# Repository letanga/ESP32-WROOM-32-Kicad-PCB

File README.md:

# ESP32-WROOM-32-Kicad-PCB
esp32开发板kicad PCB项目

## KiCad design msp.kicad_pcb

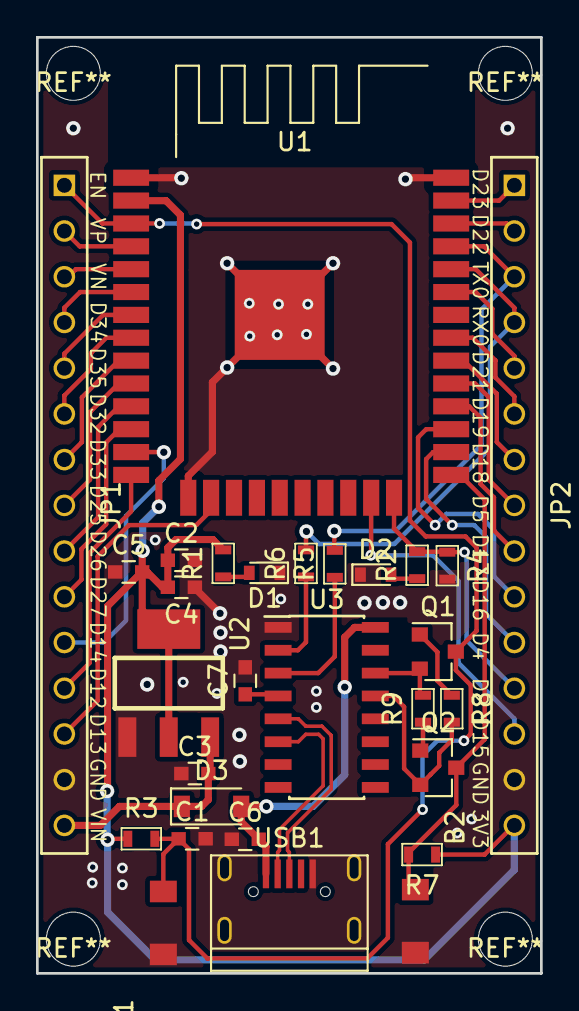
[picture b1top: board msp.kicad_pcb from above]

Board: 2 copper layers, 28.0 x 52.0 mm, 29 parts (0 on the bottom side), 42 nets.

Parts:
B1, B2: Button_2; buttton-2P
C1: 10uf; C_0603
C2, C5: 0.1uF; C_0603
C3, C4: 10uF; C_0603
C6, C7: 0.1UF; C_0603
D1, D2: LED; D_0603
D3: S4; D_SOD-123
JP1, JP2: JACK_PIN15; DIP-1.5Hole-2.54mm-Pitch-15P
Q1, Q2: S8050; SOT-23
R1, R2, R5, R6: 1K; R_0603
R3, R4, R7: 10K; R_0603
R8, R9: 10k; R_0603
U1: ESP32; ESP32-WROOM-32
U2: AMS1117-3.3; SOT-223
U3: CH340C; SOIC-16_3.9x9.9mm_Pitch1.27mm
USB1: Micro-B-USB; USB_Micro-B

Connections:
+3V3: C2.1, C4.2, C5.2, JP2.15, R1.2, R3.1, R7.1, U1.2, U2.2
/ESP32/D+: U3.5, USB1.3
/ESP32/D-: U3.6, USB1.2
/ESP32/DTR: Q2.2, R8.2, U3.13
/ESP32/EN: B1.2, C1.1, JP1.1, Q1.3, R3.2, U1.3
/ESP32/IO0: B2.1, Q2.3, R7.2, U1.25
/ESP32/IO1: JP2.3, R5.2, U1.35
/ESP32/IO2: JP2.12, R2.2, R4.1, U1.24
/ESP32/IO3: JP2.4, R6.2, U1.34
/ESP32/IO4: JP2.11, U1.26
/ESP32/IO5: JP2.8, U1.29
/ESP32/IO12: JP1.12, U1.14
/ESP32/IO13: JP1.13, U1.16
/ESP32/IO14: JP1.11, U1.13
/ESP32/IO15: JP2.13, U1.23
/ESP32/IO16: JP2.10, U1.27
/ESP32/IO17: JP2.9, U1.28
/ESP32/IO18: JP2.7, U1.30
/ESP32/IO19: JP2.6, U1.31
/ESP32/IO21: JP2.5, U1.33
/ESP32/IO22: JP2.2, U1.36
/ESP32/IO23: JP2.1, U1.37
/ESP32/IO25: JP1.8, U1.10
/ESP32/IO26: JP1.9, U1.11
/ESP32/IO27: JP1.10, U1.12
/ESP32/IO32: JP1.6, U1.8
/ESP32/IO33: JP1.7, U1.9
/ESP32/IO34: JP1.4, U1.6
/ESP32/IO35: JP1.5, U1.7
/ESP32/IO36: JP1.2, U1.4
/ESP32/IO39: JP1.3, U1.5
/ESP32/RTS: Q1.2, R9.2, U3.14
/ESP32/RXD: R6.1, U3.2
/ESP32/TXD: R5.1, U3.3
GND: B1.1, B2.2, C1.2, C2.2, C3.1, C4.1, C5.1, C6.1, C7.2, D1.1, D2.1, JP1.14, JP2.14, R4.2, U1.1, U1.15, U1.38, U1.39, U2.1, U3.1, USB1.5, USB1.6, USB1.7
unnamed: C7.1, U3.4
unnamed: D1.2, R1.1
unnamed: D2.2, R2.1
unnamed: Q1.1, R8.1
unnamed: Q2.1, R9.1
VBUS: C6.2, D3.2, U3.16, USB1.1
VIN: C3.2, D3.1, JP1.15, U2.3

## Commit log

2021-11-10 上传PCB文件
